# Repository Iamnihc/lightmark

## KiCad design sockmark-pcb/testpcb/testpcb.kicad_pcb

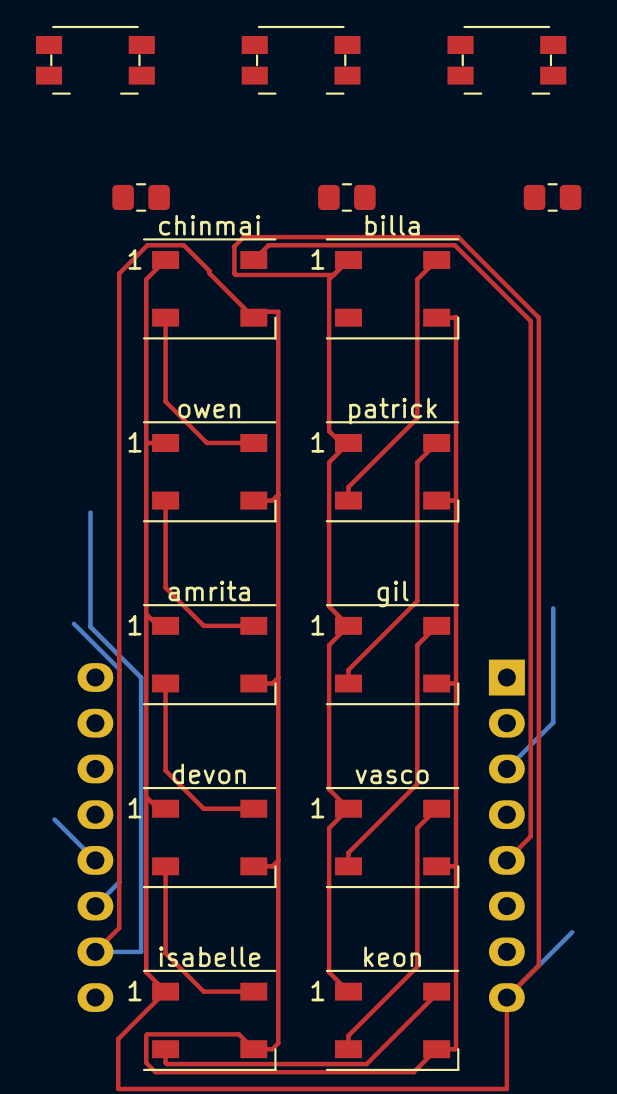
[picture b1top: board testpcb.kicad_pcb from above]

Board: 2 copper layers, 17 parts (1 on the bottom side), 15 nets.

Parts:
:P: SW_SPST; Panasonic_EVQPUK_EVQPUB
U1: WeMos_D1_mini; WEMOS_D1_mini_light
amrita: WS2812B; LED_WS2812B_PLCC4_5.0x5.0mm_P3.2mm
billa: WS2812B; LED_WS2812B_PLCC4_5.0x5.0mm_P3.2mm
brightness: SW_SPST; Panasonic_EVQPUK_EVQPUB
chinmai: WS2812B; LED_WS2812B_PLCC4_5.0x5.0mm_P3.2mm
color: SW_SPST; Panasonic_EVQPUK_EVQPUB
devon: WS2812B; LED_WS2812B_PLCC4_5.0x5.0mm_P3.2mm
gil: WS2812B; LED_WS2812B_PLCC4_5.0x5.0mm_P3.2mm
isabelle: WS2812B; LED_WS2812B_PLCC4_5.0x5.0mm_P3.2mm
keon: WS2812B; LED_WS2812B_PLCC4_5.0x5.0mm_P3.2mm
owen: WS2812B; LED_WS2812B_PLCC4_5.0x5.0mm_P3.2mm
patrick: WS2812B; LED_WS2812B_PLCC4_5.0x5.0mm_P3.2mm
r_brightness: R_Small; R_0805_2012Metric_Pad1.20x1.40mm_HandSolder
r_color: R_Small; R_0805_2012Metric_Pad1.20x1.40mm_HandSolder
r_main: R_Small; R_0805_2012Metric_Pad1.20x1.40mm_HandSolder
vasco: WS2812B; LED_WS2812B_PLCC4_5.0x5.0mm_P3.2mm

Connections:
+3V3: :P.1, U1.8, amrita.1, billa.1, brightness.1, chinmai.1, color.1, devon.1, gil.1, isabelle.1, keon.1, owen.1, patrick.1, vasco.1
GND: U1.10, amrita.3, billa.3, chinmai.3, devon.3, gil.3, isabelle.3, keon.3, owen.3, patrick.3, vasco.3
unnamed: isabelle.2, keon.4
unnamed: devon.2, isabelle.4
unnamed: U1.3, color.2
unnamed: U1.12, brightness.2
unnamed: :P.2, U1.11
unnamed: amrita.2, devon.4
unnamed: amrita.4, owen.2
unnamed: billa.4, patrick.2
unnamed: chinmai.2, owen.4
unnamed: gil.2, patrick.4
unnamed: gil.4, vasco.2
unnamed: keon.2, vasco.4
led_sig_in: U1.5, chinmai.4

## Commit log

2020-11-22 lemme push real quick
2020-11-22 whops im using my windows files
2020-11-22 whops apparenlty this is how arduino works
2020-11-22 the code finally uploads!
2020-11-24 testing more stuff out
2020-11-24 maybe i shouldnt commit that
2020-12-01 some random changes
